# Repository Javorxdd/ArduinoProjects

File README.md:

# ArduinoProjects
All my ArduinoProjects, free to use. In some projects you need to use libraries with a .zip extension.

Adafruit_NeoPixel use NeoPixel LED light like NeoPixel WS2812B, NeoPixel WS2812...

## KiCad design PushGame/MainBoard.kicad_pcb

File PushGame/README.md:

# PushGame

> [!IMPORTANT]
> Česká verze se nachází pod anglickou

> [!NOTE]
> Photos below the text

## Hey! Hey!

I created this game just for you! A simple game where the player has to click a button as many as 60 times (depending on your settings) and gradually, during his score, such LED “bulbs” will light up. If he's the fastest, he'll get a fanfare as a reward, or feel free to give him one. Everything you need for this game is in this repository. The PCB tells you what to plug in where. The choice of parts is up to you, but I recommend leaving the ones I've picked out for you. All you have to do is calculate the resistor for the LED panel, which depends on your chosen color and supply voltage.

The parts list for the main board:
1. 9x BC337 transistor,
2. 3x 10kOhm resistor,
3. 9x 1kOhm resistor,
4. 1x LM7805,
5. 1x Fuse (also fuse case -> this is all optional, but protection is always useful),
6. 1x 100n capacitor
7. 1x 330n capacitor (can be replaced by a 470n capacitor)

Parts list for the LED panel:
1. 4x LED diode
2. 1x resistor (value depends on the power supply voltage you choose and the color of the LED)

and then of course some wiring :)

I recommend a maximum voltage of 24 V (LM78 regulator can handle 30 V max, but I recommend a reserve. You don't need to put a heatsink, but if you do, it won't hurt anything). If you have any questions or comments you can contact me at:

Discord: @javorovotoje

Instagram: [@javorovotoje](https://instagram.com/javorovotoje)

> [!CAUTION]
> The author assumes no liability if injury or fire occurs as a result of improper handling!

## Ahoj!

> [!NOTE]
> Fotografie pod textem

vytvořil jsem tuto hru třeba právě pro tebe! Jednoduchá hra, kde hráč musí co nejdříve 60x (záleží na tvém nastavení) kliknout tlačítkem a postupně se mu během jeho skóre budou rozsvícet takové LED "žárovky". Pokud bude co nejrychlejší, zahraje mu za odměnu fanfára, nebo mu klidně můžeš nějakou věnovat. Vše, co k této hře potřebuješ máš v tomto repozitáři. Na PCB máš popsané vše, co kam připojit. Výběr součástek je na tobě, ale doporučuji zanechat ty, které jsem ti vybral. Jediné, co musíš udělat je vypočítat si rezistor pro LED panel, který závisí na tvé zvolené barvě a napájecím napětí.

List součástek pro hlavní desku:
1. 9x tranzistor BC337,
2. 3x 10kOhm rezistor,
3. 9x 1kOhm rezistor,
4. 1x LM7805,
5. 1x Pojistka (zároveň i pojistkové pouzdro -> toto celé je volitelné, ale ochrana se vždy hodí),
6. 1x 100n kondenzátor
7. 1x 330n kondenzátor (může být nahrazen kondenzátorem 470n)

List součástek pro LED panel:
1. 4x LED dioda
2. 1x rezistor (hodnota závisí na tebou zvoleným napájecím napětí a barvou LED diody)

a poté samozřejmě nějaká kabeláž :)

Maximální napětí doporučuji 24 V (LM78 stabilizátor zvládne max 30 V, ale doporučuji rezervu. Chladič dávat nemusíš, ale pokud ho dáš, ničemu tím neuškodíš.) V případě dotazů, nebo nějakých připomínek mne můžeš kontaktovat na:

Discordu: @javorovotoje

Instagramu: [@javorovotoje](https://instagram.com/javorovotoje)

> [!CAUTION]
> Autor nenese žádnou odpovědnost, pokud by důsledkem neodborného zacházení došlo k úrazu nebo požáru!

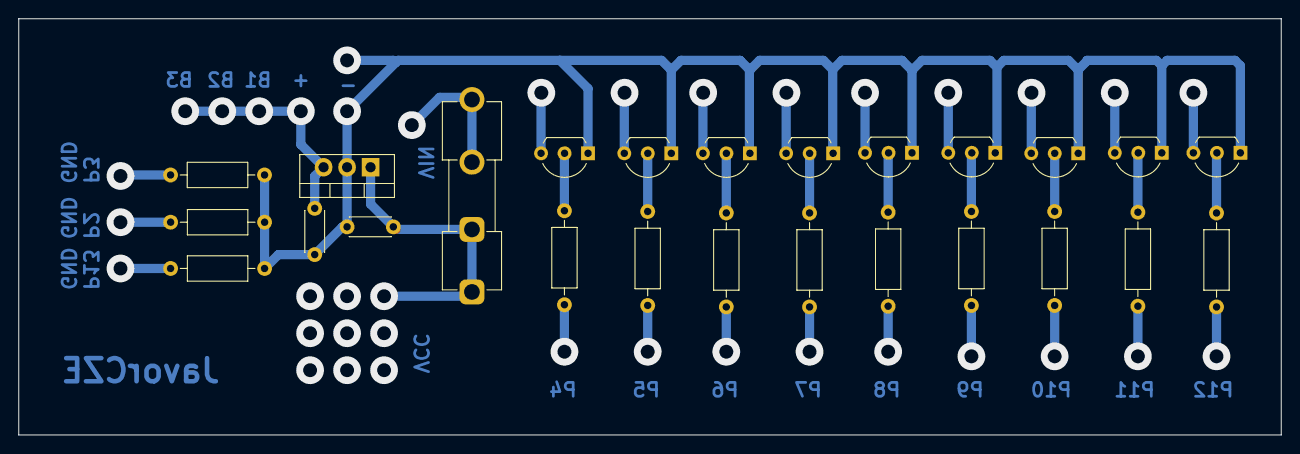
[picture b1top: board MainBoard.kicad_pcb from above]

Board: 2 copper layers, 136.5 x 45.0 mm, 25 parts (0 on the bottom side), 12 nets.

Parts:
C1: 330n; C_Disc_D4.3mm_W1.9mm_P5.00mm
C2: 100n; C_Disc_D4.3mm_W1.9mm_P5.00mm
F1: Fuse; Fuseholder_Clip-5x20mm_Eaton_1A5601-01_Inline_P20.80x6.76mm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
Q1, Q2, Q3, Q4, Q5, Q6, Q7, Q8, Q9: BC337; TO-92L_Inline_Wide
R1, R2, R3, R4, R5, R6, R7, R8, R9: 1k; R_Axial_DIN0207_L6.3mm_D2.5mm_P10.16mm_Horizontal
R10, R11, R12: 10k; R_Axial_DIN0207_L6.3mm_D2.5mm_P10.16mm_Horizontal
U1: LM7805_TO220; TO-220-3_Vertical

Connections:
unnamed: Q1.2 (B), R1.2
unnamed: C1.2, C2.2, Q1.1 (C), Q2.1 (C), Q3.1 (C), Q4.1 (C), Q5.1 (C), Q6.1 (C), Q7.1 (C), Q8.1 (C), Q9.1 (C), R10.1, R11.1, R12.1, U1.2 (GND)
unnamed: Q2.2 (B), R2.2
unnamed: Q3.2 (B), R3.2
unnamed: Q4.2 (B), R4.2
unnamed: Q5.2 (B), R5.2
unnamed: Q6.2 (B), R6.2
unnamed: Q7.2 (B), R7.2
unnamed: Q8.2 (B), R8.2
unnamed: Q9.2 (B), R9.2
unnamed: C1.1, F1.1, U1.1 (VI)
unnamed: C2.1, U1.3 (VO)

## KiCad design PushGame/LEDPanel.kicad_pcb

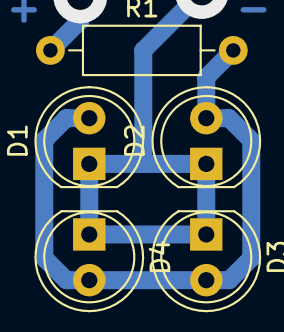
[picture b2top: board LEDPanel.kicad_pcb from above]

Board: 2 copper layers, 5 parts (0 on the bottom side), 2 nets.

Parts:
D1, D2, D3, D4: LED; LED_D5.0mm
R1: 100; R_Axial_DIN0207_L6.3mm_D2.5mm_P10.16mm_Horizontal

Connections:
unnamed: D1.2 (A), D2.2 (A), D3.2 (A), D4.2 (A), R1.2
unnamed: D1.1 (K), D2.1 (K), D3.1 (K), D4.1 (K)

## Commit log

2023-02-25 Create colours.cpp
    I'm using Arduino Pro Mini, with Adafruit NeoPixel with 7 LED. You need Adafruit NeoPixel library.
2023-02-25 Rename barvicky.ino to colours.ino
    This is format for Arduino IDE
2025-06-11 Update PushGame.ino
    Added debounce time for properly reading pushing button
